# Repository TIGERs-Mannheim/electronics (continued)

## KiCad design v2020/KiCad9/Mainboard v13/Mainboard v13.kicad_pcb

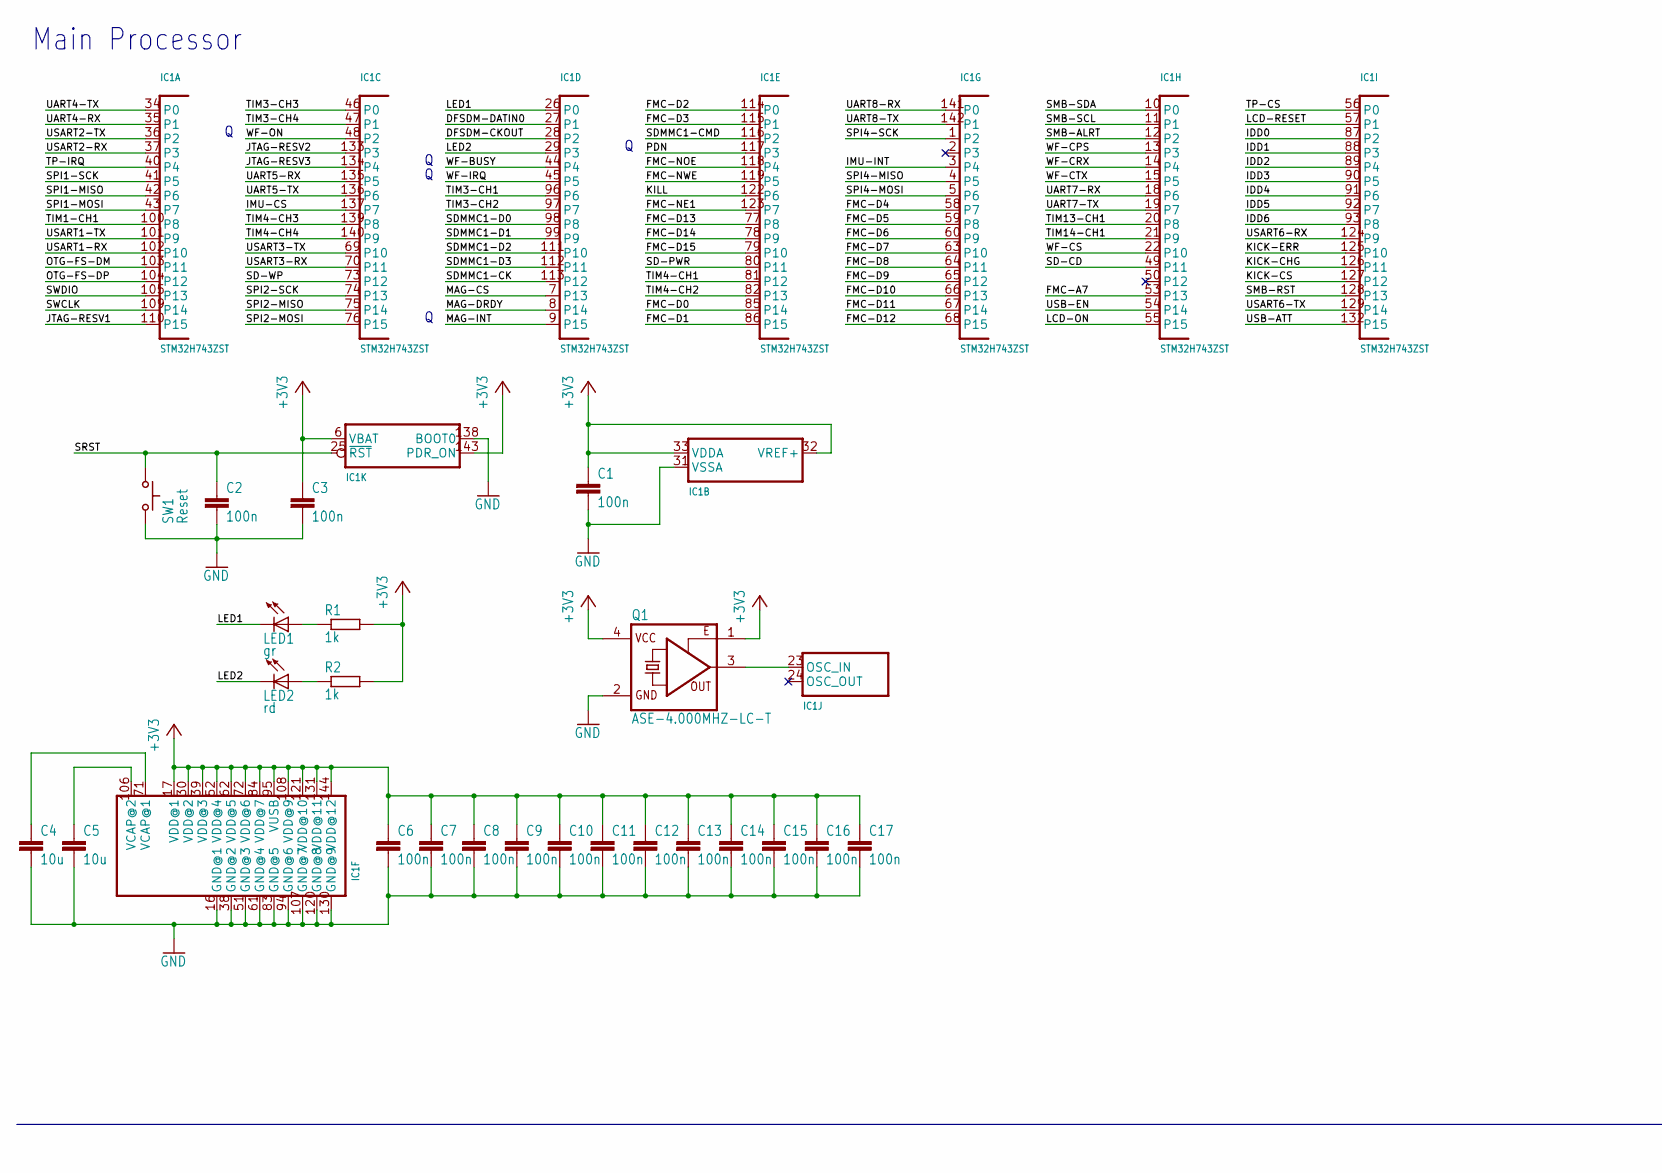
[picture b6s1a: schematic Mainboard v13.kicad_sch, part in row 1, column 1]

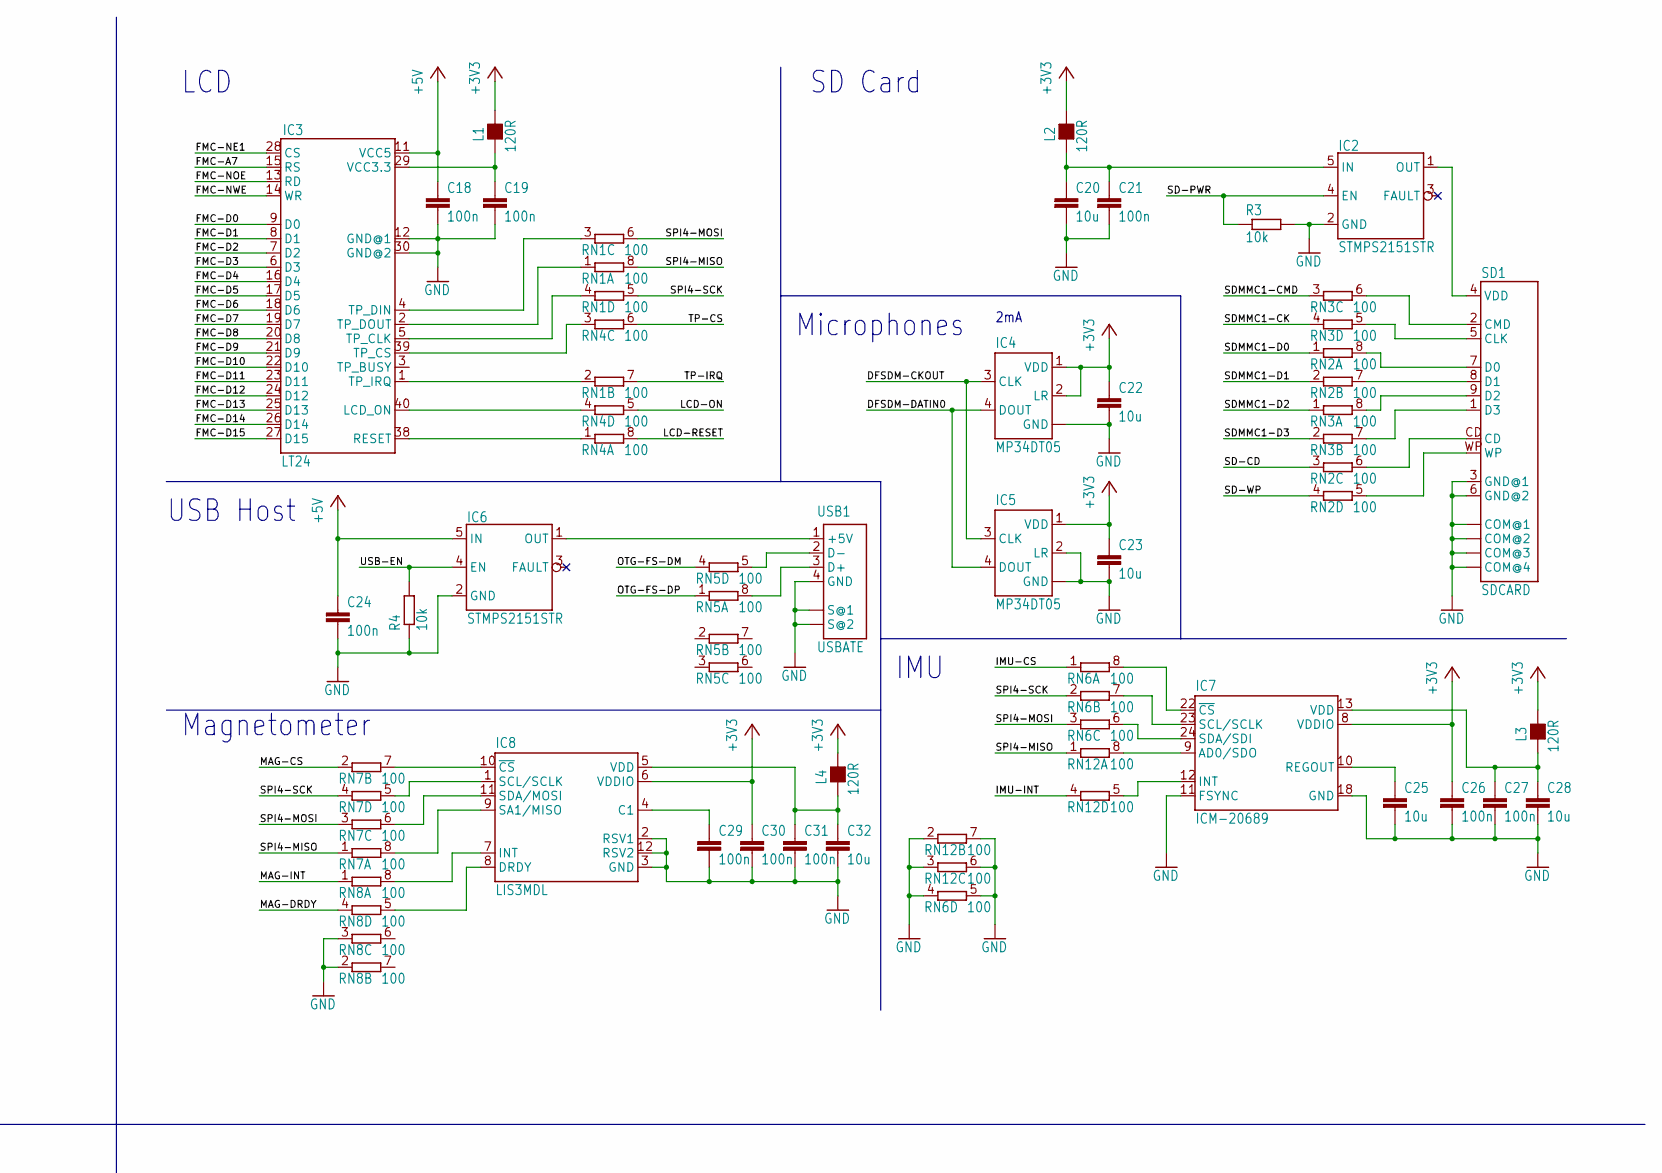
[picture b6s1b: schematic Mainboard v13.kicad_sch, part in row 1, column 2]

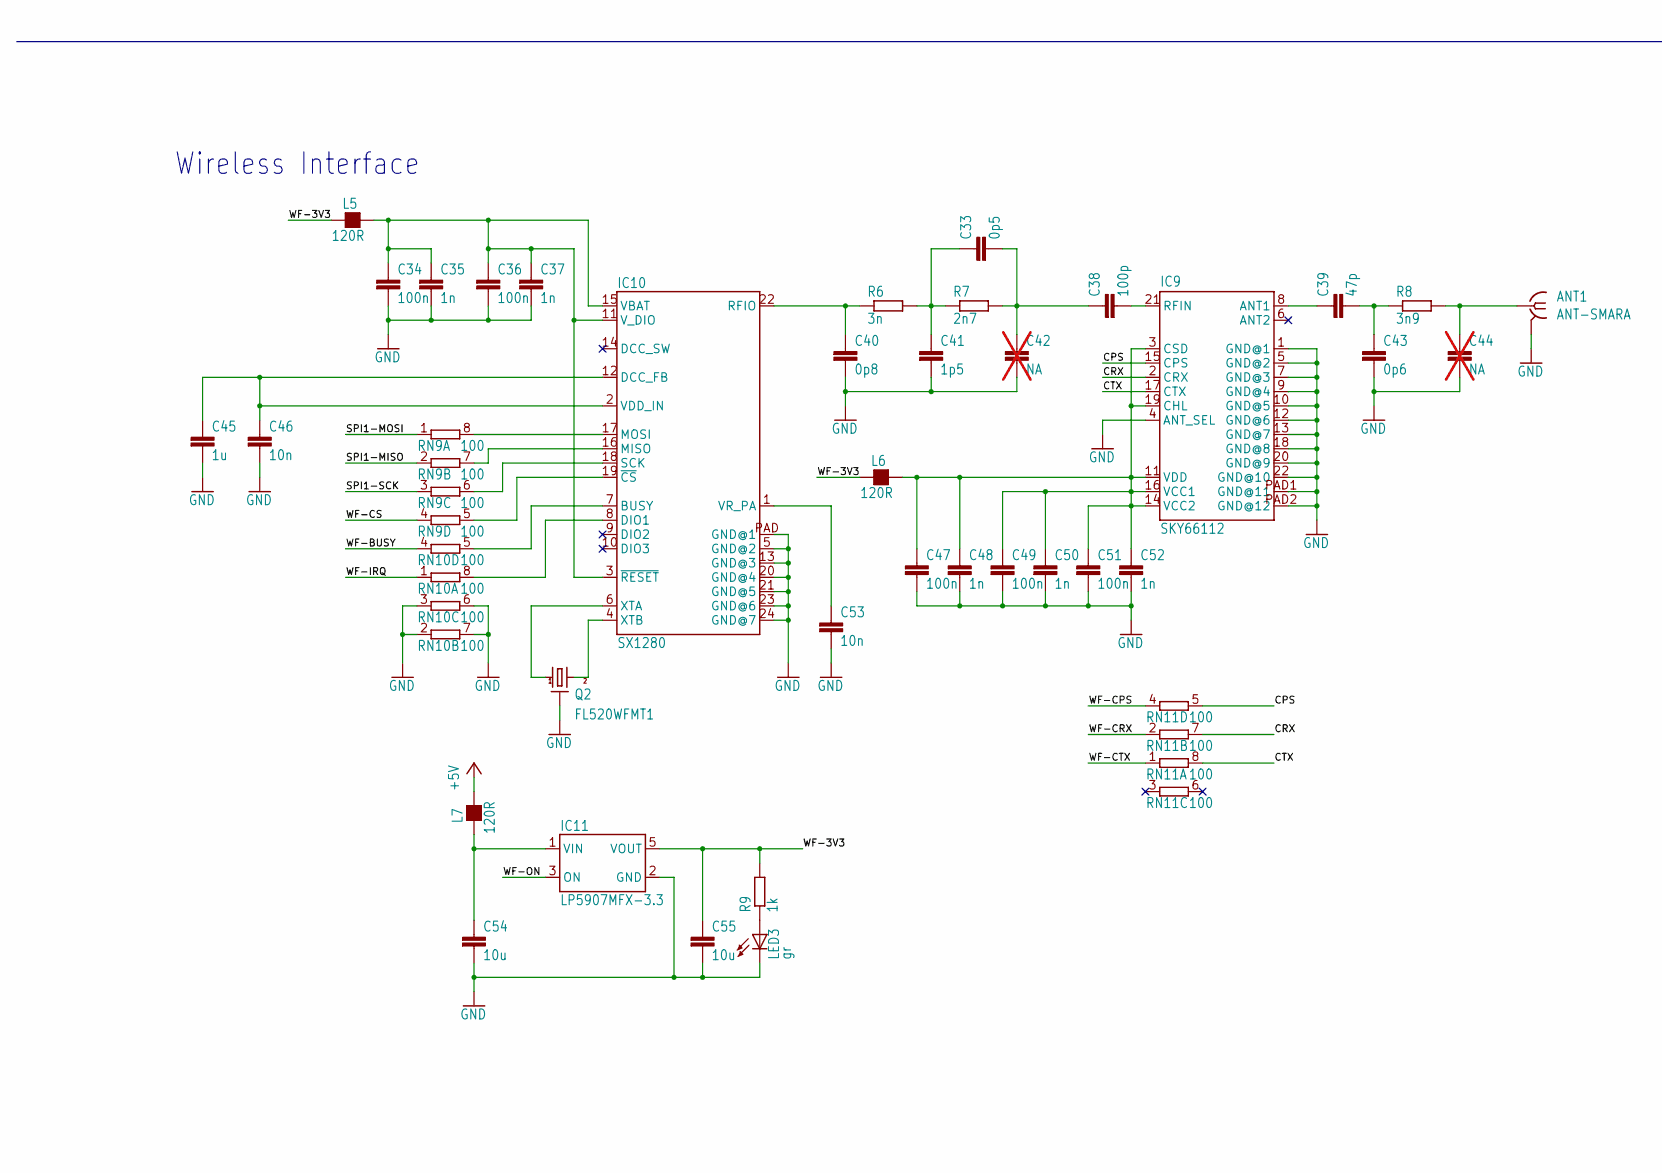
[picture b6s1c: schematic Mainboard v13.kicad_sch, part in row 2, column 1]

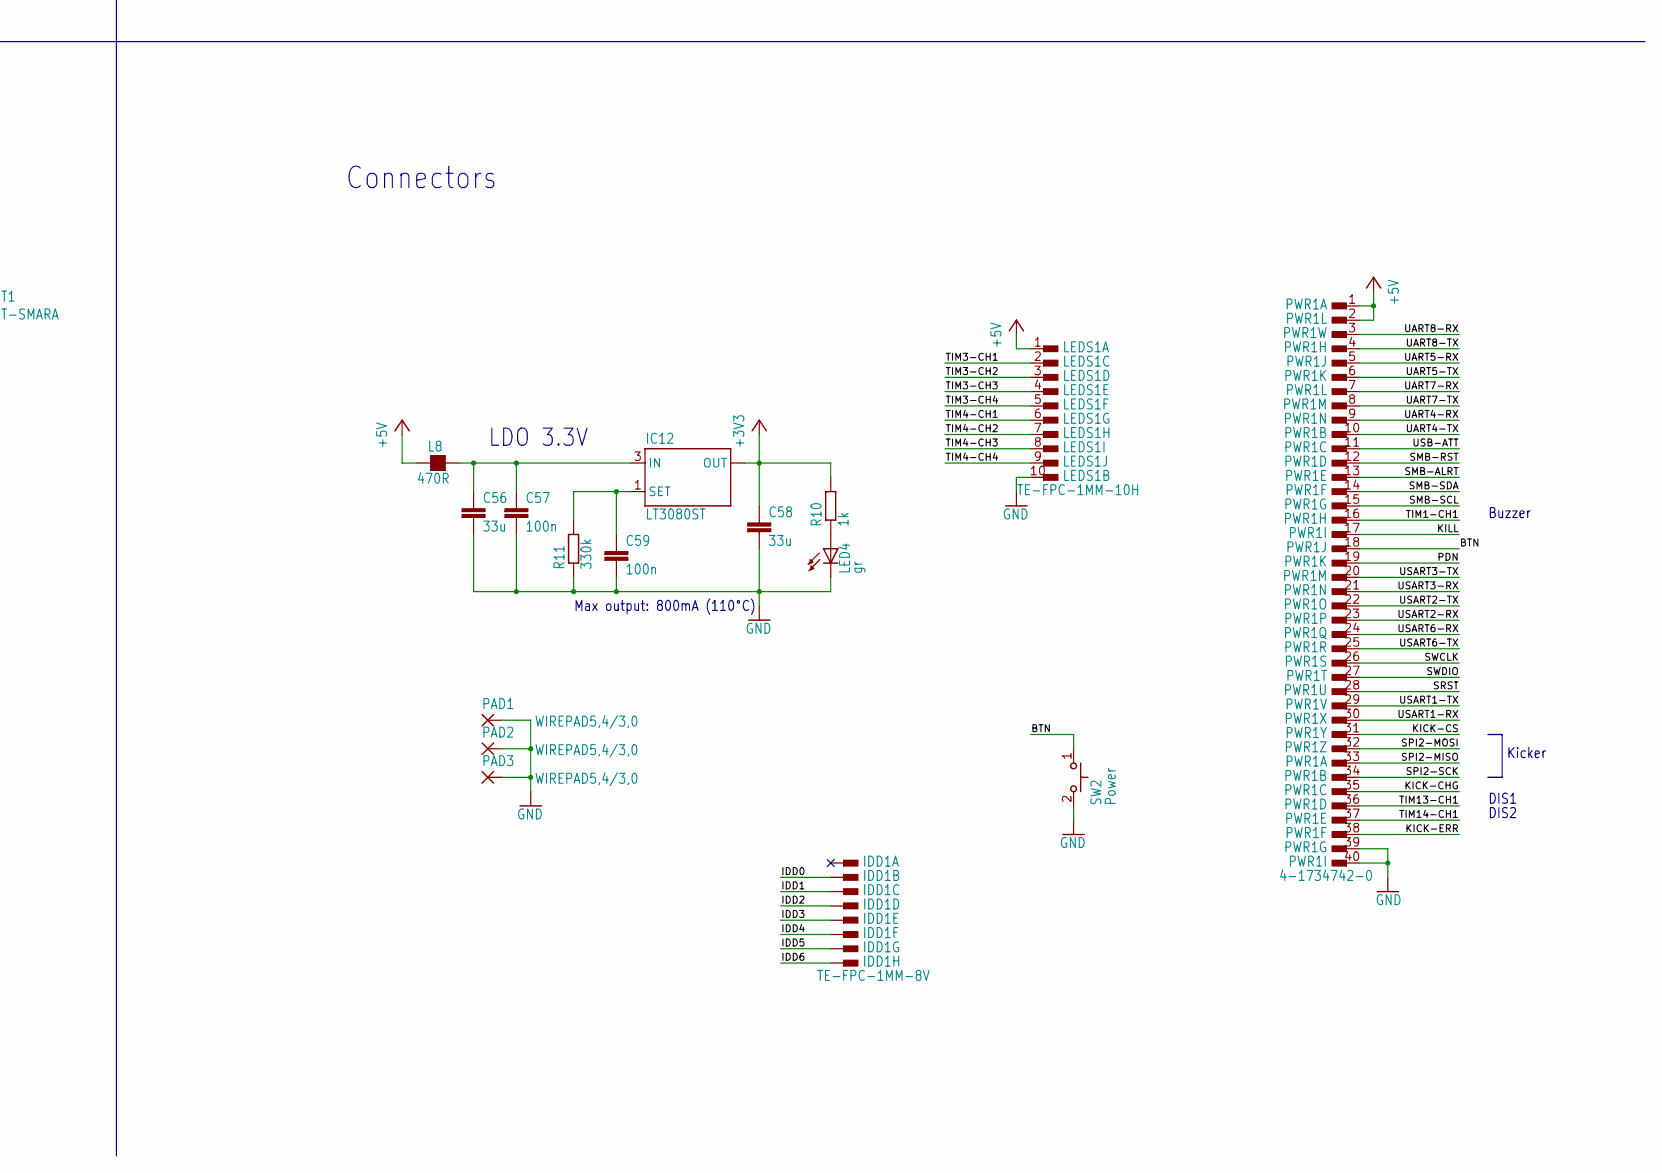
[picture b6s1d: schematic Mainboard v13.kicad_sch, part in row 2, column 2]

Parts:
ANT1: ANT-SMARA; ANT-SMA-RA; Digi-Key A97593-ND
C1, C2, C3, C6, C7, C8, C9, C10, C11, C12, C13, C14, C15, C16, C17, C18, C19, C21, C24, C26, C27, C29, C30, C31, C34, C36, C47, C49, C51, C57, C59: 100n; C0603; Digi-Key 1292-1397-1-ND
C4, C5, C20, C22, C23, C25, C28, C32, C54, C55: 10u; C0603; Digi-Key 478-5318-1-ND
C33: 0p5; C0402
C35, C37, C48, C50, C52: 1n; C0603; Digi-Key 399-1083-1-ND
C38: 100p; C0402
C39: 47p; C0402
C40: 0p8; C0402
C41: 1p5; C0402
C42, C44: NA; C0402; not fitted
C43: 0p6; C0402
C45: 1u; C0603; Digi-Key 1276-1860-1-ND
C46, C53: 10n; C0603; Digi-Key 399-1091-1-ND
C56, C58: 33u; C1206; Digi-Key 445-8046-1-ND
IC1: STM32H743ZST; LQFP144-ST; Digi-Key 497-17721-ND
IC2, IC6: STMPS2151STR; SOT23-5; Digi-Key 497-6856-1-ND
IC3: LT24; Digi-Key P0185-ND
IC4, IC5: MP34DT05; HCLGA4; Digi-Key 497-17809-1-ND
IC7: ICM-20689; QFN24-4X4-P; Digi-Key 1428-1059-1-ND
IC8: LIS3MDL; VFLGA-12; Digi-Key 497-13892-1-ND
IC9: SKY66112; SMCM-22; Digi-Key 863-1803-1-ND
IC10: SX1280; QFN24L; Digi-Key SX1280IMLTRTCT-ND
IC11: LP5907MFX-3.3; SOT23-5L; Digi-Key 296-38557-1-ND
IC12: LT3080ST; SOT223; Digi-Key LT3080EST#PBF-ND
IDD1: TE-FPC-1MM-8V; TE-1734248-8; Digi-Key WM6761CT-ND
L1, L2, L3, L4, L5, L6, L7: 120R; L0603; Digi-Key 490-1037-1-ND
L8: 470R; L1206; Digi-Key 490-16530-1-ND
LED1, LED3, LED4: gr; CHIP-LED0603; Digi-Key 732-4980-1-ND
LED2: rd; CHIP-LED0603; Digi-Key 732-4979-1-ND
LEDS1: TE-FPC-1MM-10H; TE-1-84952-0; Digi-Key A100250CT-ND
PAD1, PAD2, PAD3: WIREPAD5,4/3,0; 5,4_3,0; Digi-Key 732-7085-1-ND
PWR1: 4-1734742-0; TE-4-1734592-0; Digi-Key A100226CT-ND
Q1: ASE-4.000MHZ-LC-T; OSCI-ASE; Digi-Key 1253-1550-1-ND
Q2: FL520WFMT1; CRYSTAL-7M; Digi-Key FL520WFMT1CT-ND
R1, R2, R9, R10: 1k; R0603; Digi-Key 311-1.00KHRCT-ND
R3, R4: 10k; R0603; Digi-Key 311-10.0KHRCT-ND
R6: 3n; R0402
R7: 2n7; R0402
R8: 3n9; R0402
R11: 330k; R0603; Digi-Key YAG1637CT-ND
RN1, RN2, RN3, RN4, RN5, RN6, RN7, RN8, RN9, RN10, RN11, RN12: 100; EXB28V; Digi-Key Y7101CT-ND
SD1: SDCARD; Digi-Key A101492CT-ND
SW1: Reset; BUTTON4; Digi-Key 450-1130-ND
SW2: Power; KT11; Digi-Key CKN1859CT-ND
USB1: USBATE; USBA-TE; Digi-Key A118230CT-ND

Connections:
+3V3: C1.1, C3.1, C6.1, C7.1, C8.1, C9.1, C10.1, C11.1, C12.1, C13.1, C14.1, C15.1, C16.1, C17.1, C22.1, C23.1, C26.1, C30.1, C58.1, IC1.6 (VBAT), IC1.17 (VDD@1), IC1.30 (VDD@2), IC1.32 (VREF+), IC1.33 (VDDA), IC1.39 (VDD@3), IC1.52 (VDD@4), IC1.62 (VDD@5), IC1.72 (VDD@6), IC1.84 (VDD@7), IC1.95 (VUSB), IC1.108 (VDD@9), IC1.121 (VDD@10), IC1.131 (VDD@11), IC1.143 (PDR_ON), IC1.144 (VDD@12), IC4.1 (VDD), IC4.2 (LR), IC5.1 (VDD), IC7.8 (VDDIO), IC8.6 (VDDIO), IC12.2 (OUT), IC12.4 (OUT), L1.2, L2.2, L3.2, L4.2, Q1.1 (OE), Q1.4 (VCC), R1.2, R2.2, R10.2
+5V: C18.1, C24.1, IC3.11 (VCC5), IC6.5 (IN), L7.2, L8.1, LEDS1.1 (-1), PWR1.1 (-1), PWR1.2 (-1)
/BTN: PWR1.18 (-1), SW2.1
/CPS: IC9.15 (CPS), RN11.5 (2)
/CRX: IC9.2 (CRX), RN11.7 (2)
/CTX: IC9.17 (CTX), RN11.8 (2)
/DFSDM-CKOUT: IC1.28 (P2), IC4.3 (CLK), IC5.3 (CLK)
/DFSDM-DATIN0: IC1.27 (P1), IC4.4 (DOUT), IC5.4 (DOUT)
/FMC-A7: IC1.53 (P13), IC3.15 (RS)
/FMC-D0: IC1.85 (P14), IC3.9 (D0)
/FMC-D1: IC1.86 (P15), IC3.8 (D1)
/FMC-D2: IC1.114 (P0), IC3.7 (D2)
/FMC-D3: IC1.115 (P1), IC3.6 (D3)
/FMC-D4: IC1.58 (P7), IC3.16 (D4)
/FMC-D5: IC1.59 (P8), IC3.17 (D5)
/FMC-D6: IC1.60 (P9), IC3.18 (D6)
/FMC-D7: IC1.63 (P10), IC3.19 (D7)
/FMC-D8: IC1.64 (P11), IC3.20 (D8)
/FMC-D9: IC1.65 (P12), IC3.21 (D9)
/FMC-D10: IC1.66 (P13), IC3.22 (D10)
/FMC-D11: IC1.67 (P14), IC3.23 (D11)
/FMC-D12: IC1.68 (P15), IC3.24 (D12)
/FMC-D13: IC1.77 (P8), IC3.25 (D13)
/FMC-D14: IC1.78 (P9), IC3.26 (D14)
/FMC-D15: IC1.79 (P10), IC3.27 (D15)
/FMC-NE1: IC1.123 (P7), IC3.28 (CS)
/FMC-NOE: IC1.118 (P4), IC3.13 (RD)
/FMC-NWE: IC1.119 (P5), IC3.14 (WR)
/IDD0: IC1.87 (P2), IDD1.A2 (-1), IDD1.B2 (-1)
/IDD1: IC1.88 (P3), IDD1.A3 (-1), IDD1.B3 (-1)
/IDD2: IC1.89 (P4), IDD1.A4 (-1), IDD1.B4 (-1)
/IDD3: IC1.90 (P5), IDD1.A5 (-1), IDD1.B5 (-1)
/IDD4: IC1.91 (P6), IDD1.A6 (-1), IDD1.B6 (-1)
/IDD5: IC1.92 (P7), IDD1.A7 (-1), IDD1.B7 (-1)
/IDD6: IC1.93 (P8), IDD1.A8 (-1), IDD1.B8 (-1)
/IMU-CS: IC1.137 (P7), RN6.1
/IMU-INT: IC1.3 (P4), RN12.4 (1)
/JTAG-RESV1: IC1.110 (P15)
/JTAG-RESV2: IC1.133 (P3)
/JTAG-RESV3: IC1.134 (P4)
/KICK-CHG: IC1.126 (P11), PWR1.35 (-1)
/KICK-CS: IC1.127 (P12), PWR1.31 (-1)
/KICK-ERR: IC1.125 (P10), PWR1.38 (-1)
/KILL: IC1.122 (P6), PWR1.17 (-1)
/LCD-ON: IC1.55 (P15), RN4.5 (2)
/LCD-RESET: IC1.57 (P1), RN4.8 (2)
/LED1: IC1.26 (P0), LED1.C
/LED2: IC1.29 (P3), LED2.C
/MAG-CS: IC1.7 (P13), RN7.2 (1)
/MAG-DRDY: IC1.8 (P14), RN8.4 (1)
/MAG-INT: IC1.9 (P15), RN8.1
/OTG-FS-DM: IC1.103 (P11), RN5.4 (1)
/OTG-FS-DP: IC1.104 (P12), RN5.1
/PDN: IC1.117 (P3), PWR1.19 (-1)
/SD-CD: IC1.49 (P11), RN2.3 (1)
/SD-PWR: IC1.80 (P11), IC2.4 (EN), R3.1
/SD-WP: IC1.73 (P12), RN2.4 (1)
/SDMMC1-CK: IC1.113 (P12), RN3.4 (1)
/SDMMC1-CMD: IC1.116 (P2), RN3.3 (1)
/SDMMC1-D0: IC1.98 (P8), RN2.1
/SDMMC1-D1: IC1.99 (P9), RN2.2 (1)
/SDMMC1-D2: IC1.111 (P10), RN3.1
/SDMMC1-D3: IC1.112 (P11), RN3.2 (1)
/SMB-ALRT: IC1.12 (P2), PWR1.13 (-1)
/SMB-RST: IC1.128 (P13), PWR1.12 (-1)
/SMB-SCL: IC1.11 (P1), PWR1.15 (-1)
/SMB-SDA: IC1.10 (P0), PWR1.14 (-1)
/SPI1-MISO: IC1.42 (P6), RN9.2 (1)
/SPI1-MOSI: IC1.43 (P7), RN9.1
/SPI1-SCK: IC1.41 (P5), RN9.3 (1)
/SPI2-MISO: IC1.75 (P14), PWR1.33 (-1)
/SPI2-MOSI: IC1.76 (P15), PWR1.32 (-1)
/SPI2-SCK: IC1.74 (P13), PWR1.34 (-1)
/SPI4-MISO: IC1.4 (P5), RN1.8 (2), RN7.1, RN12.1
/SPI4-MOSI: IC1.5 (P6), RN1.6 (2), RN6.3 (1), RN7.3 (1)
/SPI4-SCK: IC1.1 (P2), RN1.5 (2), RN6.2 (1), RN7.4 (1)
/SRST: C2.1, IC1.25 (~RST), PWR1.28 (-1), SW1.1, SW1.2 (1)
/SWCLK: IC1.109 (P14), PWR1.26 (-1)
/SWDIO: IC1.105 (P13), PWR1.27 (-1)
/TIM1-CH1: IC1.100 (P8), PWR1.16 (-1)
/TIM3-CH1: IC1.96 (P6), LEDS1.2 (-1)
/TIM3-CH2: IC1.97 (P7), LEDS1.3 (-1)
/TIM3-CH3: IC1.46 (P0), LEDS1.4 (-1)
/TIM3-CH4: IC1.47 (P1), LEDS1.5 (-1)
/TIM4-CH1: IC1.81 (P12), LEDS1.6 (-1)
/TIM4-CH2: IC1.82 (P13), LEDS1.7 (-1)
/TIM4-CH3: IC1.139 (P8), LEDS1.8 (-1)
/TIM4-CH4: IC1.140 (P9), LEDS1.9 (-1)
/TIM13-CH1: IC1.20 (P8), PWR1.36 (-1)
/TIM14-CH1: IC1.21 (P9), PWR1.37 (-1)
/TP-CS: IC1.56 (P0), RN4.6 (2)
/TP-IRQ: IC1.40 (P4), RN1.7 (2)
/UART4-RX: IC1.35 (P1), PWR1.9 (-1)
/UART4-TX: IC1.34 (P0), PWR1.10 (-1)
/UART5-RX: IC1.135 (P5), PWR1.5 (-1)
/UART5-TX: IC1.136 (P6), PWR1.6 (-1)
/UART7-RX: IC1.18 (P6), PWR1.7 (-1)
/UART7-TX: IC1.19 (P7), PWR1.8 (-1)
/UART8-RX: IC1.141 (P0), PWR1.3 (-1)
/UART8-TX: IC1.142 (P1), PWR1.4 (-1)
/USART1-RX: IC1.102 (P10), PWR1.30 (-1)
/USART1-TX: IC1.101 (P9), PWR1.29 (-1)
/USART2-RX: IC1.37 (P3), PWR1.23 (-1)
/USART2-TX: IC1.36 (P2), PWR1.22 (-1)
/USART3-RX: IC1.70 (P11), PWR1.21 (-1)
/USART3-TX: IC1.69 (P10), PWR1.20 (-1)
/USART6-RX: IC1.124 (P9), PWR1.24 (-1)
/USART6-TX: IC1.129 (P14), PWR1.25 (-1)
/USB-ATT: IC1.132 (P15), PWR1.11 (-1)
/USB-EN: IC1.54 (P14), IC6.4 (EN), R4.2
/WF-3V3: C55.1, IC11.5 (VOUT), L5.1, L6.1, R9.2
/WF-BUSY: IC1.44 (P4), RN10.4 (1)
/WF-CPS: IC1.13 (P3), RN11.4 (1)
/WF-CRX: IC1.14 (P4), RN11.2 (1)
/WF-CS: IC1.22 (P10), RN9.4 (1)
/WF-CTX: IC1.15 (P5), RN11.1
/WF-IRQ: IC1.45 (P5), RN10.1
/WF-ON: IC1.48 (P2), IC11.3 (ON)
GND: ANT1.GND1 (GND), ANT1.GND2 (GND), ANT1.GND3 (GND), ANT1.GND4 (GND), C1.2, C2.2, C3.2, C4.2, C5.2, C6.2, C7.2, C8.2, C9.2, C10.2, C11.2, C12.2, C13.2, C14.2, C15.2, C16.2, C17.2, C18.2, C19.2, C20.2, C21.2, C22.2, C23.2, C24.2, C25.2, C26.2, C27.2, C28.2, C29.2, C30.2, C31.2, C32.2, C34.2, C35.2, C36.2, C37.2, C40.2, C41.2, C42.2, C43.2, C44.2, C45.2, C46.2, C47.2, C48.2, C49.2, C50.2, C51.2, C52.2, C53.2, C54.2, C55.2, C56.2, C57.2, C58.2, C59.2, IC1.16 (GND@1), IC1.31 (VSSA), IC1.38 (GND@2), IC1.51 (GND@3), IC1.61 (GND@4), IC1.83 (GND@5), IC1.94 (GND@6), IC1.107 (GND@7), IC1.120 (GND@8), IC1.130 (GND@9), IC1.138 (BOOT0), IC2.2 (GND), IC3.12 (GND@1), IC3.30 (GND@2), IC4.G1 (GND), IC4.G2 (GND), IC4.G3 (GND), IC4.G4 (GND), IC5.2 (LR), IC5.G1 (GND), IC5.G2 (GND), IC5.G3 (GND), IC5.G4 (GND), IC6.2 (GND), IC7.11 (FSYNC), IC7.18 (GND), IC8.2 (RSV1), IC8.3 (GND), IC8.12 (RSV2), IC9.1 (GND@1), IC9.4 (ANT_SEL), IC9.5 (GND@2), IC9.7 (GND@3), IC9.9 (GND@4), IC9.10 (GND@5), IC9.12 (GND@6), IC9.13 (GND@7), IC9.18 (GND@8), IC9.20 (GND@9), IC9.22 (GND@10), IC9.PAD1 (GND@11), IC9.PAD2 (GND@12), IC10.5 (GND@2), IC10.13 (GND@3), IC10.20 (GND@4), IC10.21 (GND@5), IC10.23 (GND@6), IC10.24 (GND@7), IC10.PAD (GND@1), IC11.2 (GND), LED3.C, LED4.C, LEDS1.10 (-1), PAD1.1, PAD2.1, PAD3.1, PWR1.39 (-1), PWR1.40 (-1), Q1.2 (GND), Q2.2 (GND1), Q2.4 (GND1), R3.2, R4.1, R11.1, RN6.4 (1), RN6.5 (2), RN8.2 (1), RN8.3 (1), RN10.2 (1), RN10.3 (1), RN10.6 (2), RN10.7 (2), RN12.2 (1), RN12.3 (1), RN12.6 (2), RN12.7 (2), SD1.3 (GND@1), SD1.6 (GND@2), SD1.COM1 (COM@1), SD1.COM2 (COM@2), SD1.COM3 (COM@3), SD1.COM4 (COM@4), SW1.3 (2), SW1.4 (2), SW2.2, USB1.4 (GND), USB1.MNT1 (S@1), USB1.MNT2 (S@2)
unnamed: ANT1.C (1), C44.1, R8.2
unnamed: C33.1, C41.1, R6.2, R7.1
unnamed: C33.2, C38.1, C42.1, R7.2
unnamed: C39.2, C43.1, R8.1
unnamed: C4.1, IC1.71 (VCAP@1)
unnamed: C5.1, IC1.106 (VCAP@2)
unnamed: IC1.23 (OSC_IN), Q1.3 (FO)
unnamed: C20.1, C21.1, IC2.5 (IN), L2.1
unnamed: IC2.1 (OUT), SD1.4 (VDD)
unnamed: IC3.40 (LCD_ON), RN4.4 (1)
unnamed: IC3.38 (RESET), RN4.1
unnamed: IC3.5 (TP_CLK), RN1.4 (1)
unnamed: IC3.39 (TP_CS), RN4.3 (1)
unnamed: IC3.4 (TP_DIN), RN1.3 (1)
unnamed: IC3.2 (TP_DOUT), RN1.1
unnamed: IC3.1 (TP_IRQ), RN1.2 (1)
unnamed: C19.1, IC3.29 (VCC3.3), L1.1
unnamed: IC6.1 (OUT), USB1.1 (+5V)
unnamed: IC7.9 (AD0/SDO), RN12.8 (2)
unnamed: IC7.12 (INT), RN12.5 (2)
unnamed: C25.1, IC7.10 (REGOUT)
unnamed: IC7.23 (SCL/SCLK), RN6.7 (2)
unnamed: IC7.24 (SDA/SDI), RN6.6 (2)
unnamed: C27.1, C28.1, IC7.13 (VDD), L3.1
unnamed: IC7.22 (~CS), RN6.8 (2)
unnamed: C29.1, IC8.4 (C1)
unnamed: IC8.8 (DRDY), RN8.5 (2)
unnamed: IC8.7 (INT), RN8.8 (2)
unnamed: IC8.9 (SA1/MISO), RN7.8 (2)
unnamed: IC8.1 (SCL/SCLK), RN7.5 (2)
unnamed: IC8.11 (SDA/MOSI), RN7.6 (2)
unnamed: C31.1, C32.1, IC8.5 (VDD), L4.1
unnamed: IC8.10 (~CS), RN7.7 (2)
unnamed: C39.1, IC9.8 (ANT1)
unnamed: C47.1, C48.1, C49.1, C50.1, C51.1, C52.1, IC9.3 (CSD), IC9.11 (VDD), IC9.14 (VCC2), IC9.16 (VCC1), IC9.19 (CHL), L6.2
unnamed: C38.2, IC9.21 (RFIN)
unnamed: IC10.7 (BUSY), RN10.5 (2)
unnamed: C45.1, C46.1, IC10.2 (VDD_IN), IC10.12 (DCC_FB)
unnamed: IC10.8 (DIO1), RN10.8 (2)
unnamed: IC10.16 (MISO), RN9.7 (2)
unnamed: IC10.17 (MOSI), RN9.8 (2)
unnamed: C40.1, IC10.22 (RFIO), R6.1
unnamed: IC10.18 (SCK), RN9.6 (2)
unnamed: C34.1, C35.1, C36.1, C37.1, IC10.3 (~RESET), IC10.11 (V_DIO), IC10.15 (VBAT), L5.2
unnamed: C53.1, IC10.1 (VR_PA)
unnamed: IC10.6 (XTA), Q2.1
unnamed: IC10.4 (XTB), Q2.3 (2)
unnamed: IC10.19 (~CS), RN9.5 (2)
unnamed: C54.1, IC11.1 (VIN), L7.1
unnamed: C56.1, C57.1, IC12.3 (IN), L8.2
unnamed: C59.1, IC12.1 (SET), R11.2
unnamed: LED1.A, R1.1
unnamed: LED2.A, R2.1
unnamed: LED3.A, R9.1
unnamed: LED4.A, R10.1
unnamed: RN2.8 (2), SD1.7 (D0)
unnamed: RN2.7 (2), SD1.8 (D1)
unnamed: RN2.6 (2), SD1.CD
unnamed: RN2.5 (2), SD1.WP
unnamed: RN3.8 (2), SD1.9 (D2)
unnamed: RN3.7 (2), SD1.1 (D3)
unnamed: RN3.6 (2), SD1.2 (CMD)
unnamed: RN3.5 (2), SD1.5 (CLK)
unnamed: RN5.8 (2), USB1.3 (D+)
unnamed: RN5.5 (2), USB1.2 (D-)

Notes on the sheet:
LDO 3.3V
Max output: 800mA (110°C)
DIS2
Wireless Interface
USB Host
Kicker
IMU
Buzzer
SD Card
Connectors
DIS1
Main Processor
LCD
2mA
Magnetometer
Microphones

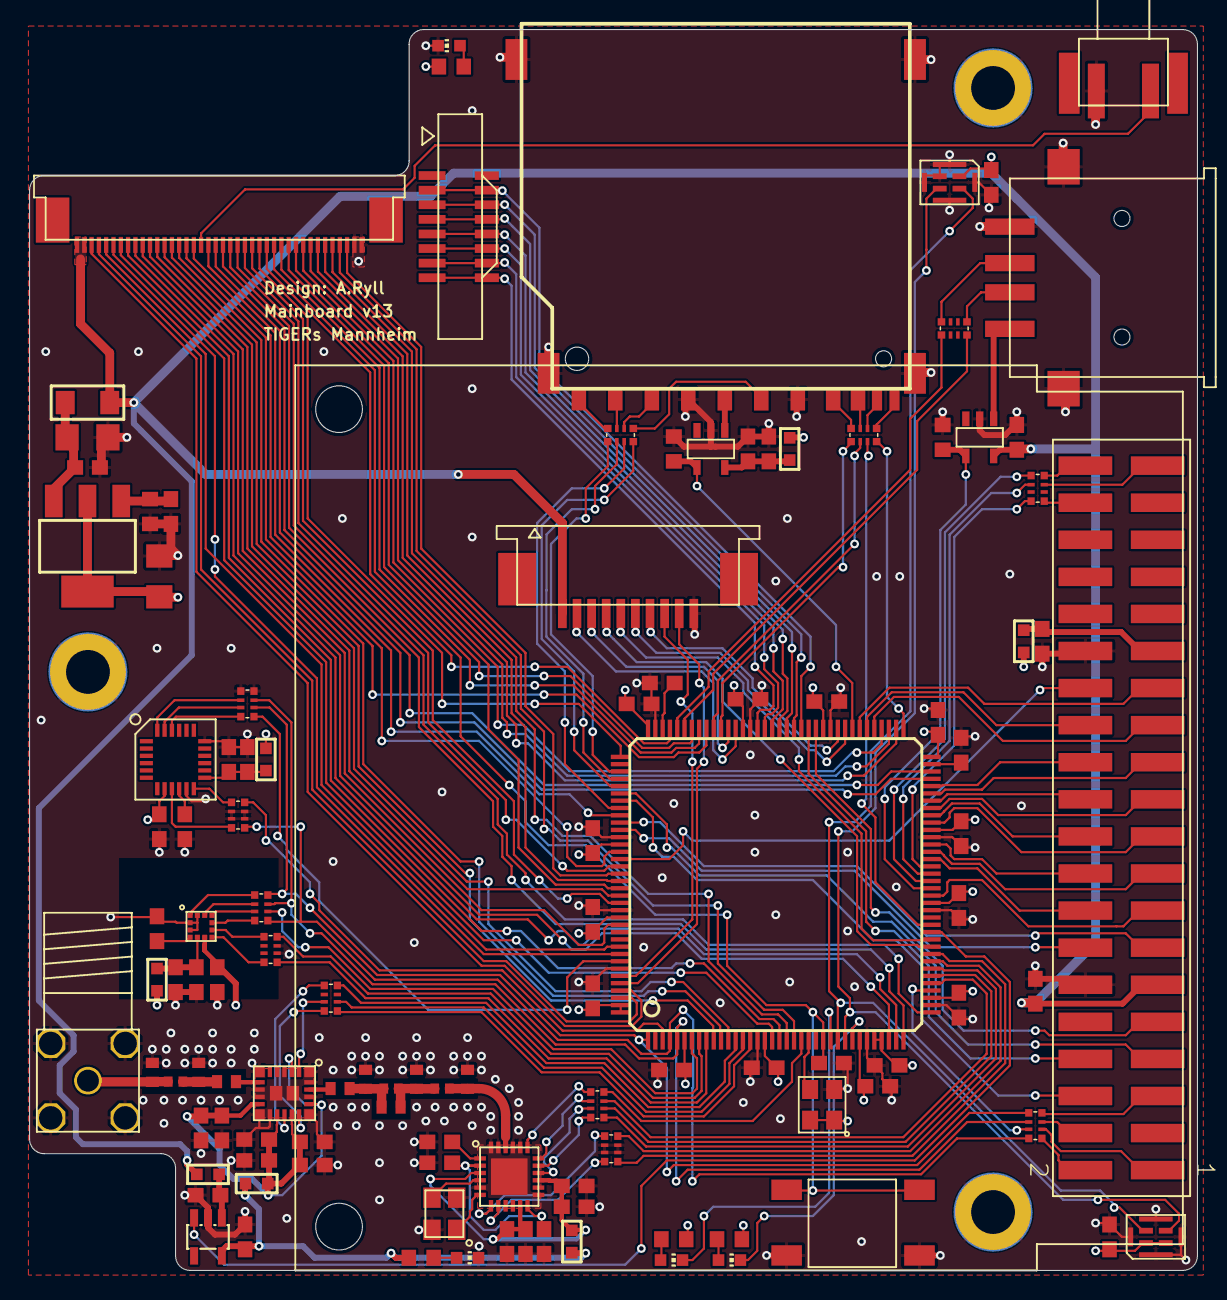
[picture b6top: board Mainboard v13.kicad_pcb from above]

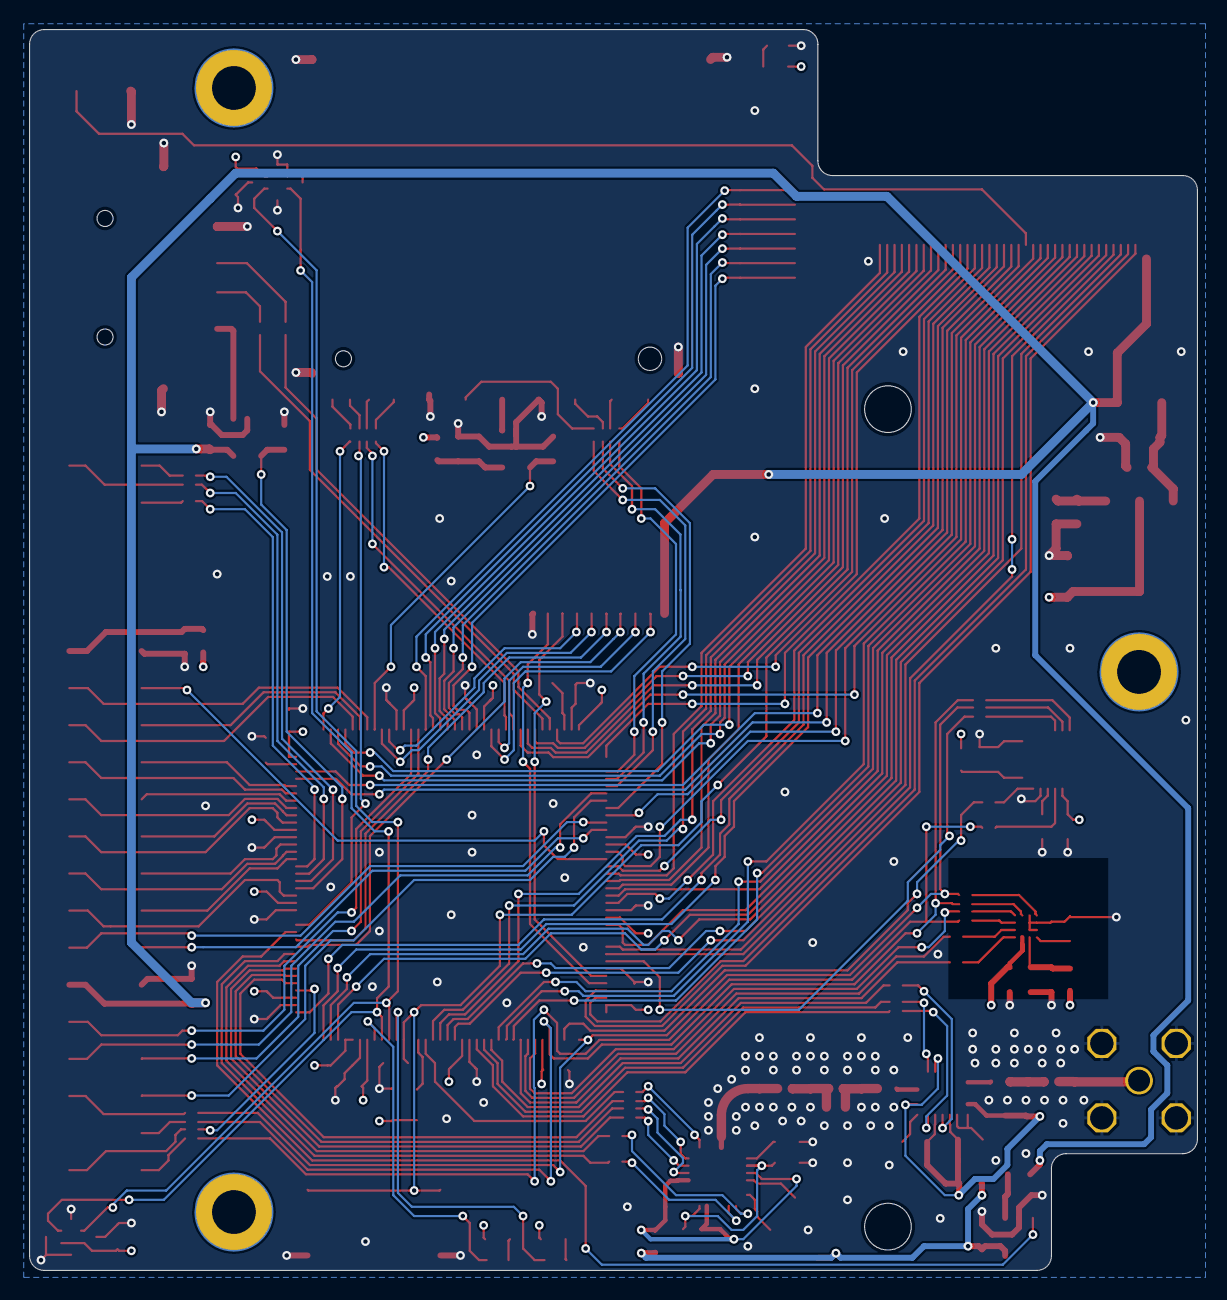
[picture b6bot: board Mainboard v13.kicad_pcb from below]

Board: 4 copper layers, 80.0 x 85.0 mm, 118 parts (3 on the bottom side), 181 nets.

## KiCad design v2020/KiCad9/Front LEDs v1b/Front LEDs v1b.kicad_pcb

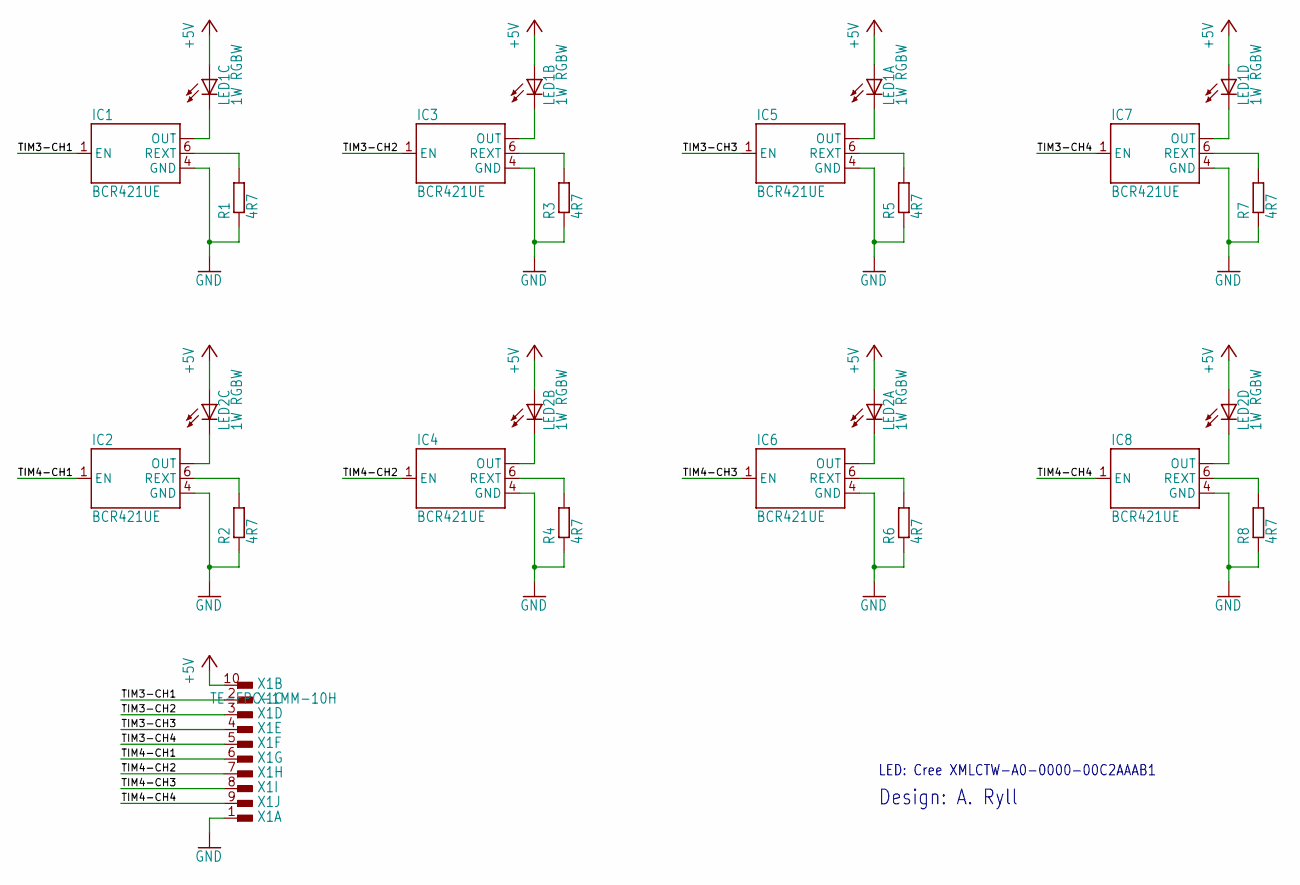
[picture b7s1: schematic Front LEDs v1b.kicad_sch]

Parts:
IC1, IC2, IC3, IC4, IC5, IC6, IC7, IC8: BCR421UE; SOT26
LED1, LED2: 1W RGBW; CREE-XLAMP; PARTNR XMLCTW-A0-0000-00C2AAAB1
R1, R2, R3, R4, R5, R6, R7, R8: 4R7; R0805
X1: TE-FPC-1MM-10H; TE-1-84952-0

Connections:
+5V: LED1.1 (A), LED1.2 (A), LED1.3 (A), LED1.4 (A), LED2.1 (A), LED2.2 (A), LED2.3 (A), LED2.4 (A), X1.10
GND: IC1.4 (GND), IC2.4 (GND), IC3.4 (GND), IC4.4 (GND), IC5.4 (GND), IC6.4 (GND), IC7.4 (GND), IC8.4 (GND), R1.1, R2.1, R3.1, R4.1, R5.1, R6.1, R7.1, R8.1, X1.1
unnamed: IC1.2 (OUT), IC1.3 (OUT), IC1.5 (OUT), LED1.8 (C)
unnamed: IC1.6 (REXT), R1.2
unnamed: IC3.2 (OUT), IC3.3 (OUT), IC3.5 (OUT), LED1.7 (C)
unnamed: IC3.6 (REXT), R3.2
unnamed: IC5.2 (OUT), IC5.3 (OUT), IC5.5 (OUT), LED1.6 (C)
unnamed: IC5.6 (REXT), R5.2
unnamed: IC7.2 (OUT), IC7.3 (OUT), IC7.5 (OUT), LED1.5 (C)
unnamed: IC7.6 (REXT), R7.2
unnamed: IC2.2 (OUT), IC2.3 (OUT), IC2.5 (OUT), LED2.8 (C)
unnamed: IC2.6 (REXT), R2.2
unnamed: IC4.2 (OUT), IC4.3 (OUT), IC4.5 (OUT), LED2.7 (C)
unnamed: IC4.6 (REXT), R4.2
unnamed: IC6.2 (OUT), IC6.3 (OUT), IC6.5 (OUT), LED2.6 (C)
unnamed: IC6.6 (REXT), R6.2
unnamed: IC8.2 (OUT), IC8.3 (OUT), IC8.5 (OUT), LED2.5 (C)
unnamed: IC8.6 (REXT), R8.2
TIM3-CH1: IC1.1 (EN), X1.2
TIM3-CH2: IC3.1 (EN), X1.3
TIM3-CH3: IC5.1 (EN), X1.4
TIM3-CH4: IC7.1 (EN), X1.5
TIM4-CH1: IC2.1 (EN), X1.6
TIM4-CH2: IC4.1 (EN), X1.7
TIM4-CH3: IC6.1 (EN), X1.8
TIM4-CH4: IC8.1 (EN), X1.9

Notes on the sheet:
LED: Cree XMLCTW-A0-0000-00C2AAAB1
Design: A. Ryll

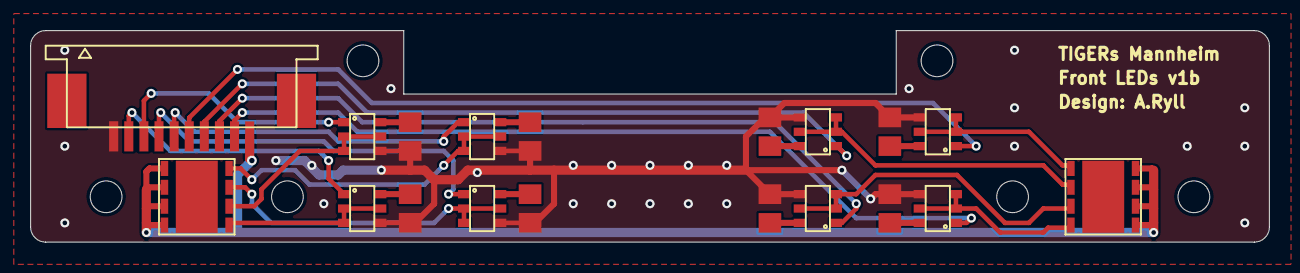
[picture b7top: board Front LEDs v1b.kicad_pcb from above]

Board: 2 copper layers, 82.0 x 14.0 mm, 25 parts (0 on the bottom side), 26 nets.

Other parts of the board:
UNK_HOLE_0: dummyfp0
UNK_HOLE_1: dummyfp1
UNK_HOLE_2: dummyfp2
UNK_HOLE_3: dummyfp3
UNK_HOLE_4: dummyfp4
UNK_HOLE_5: dummyfp5
